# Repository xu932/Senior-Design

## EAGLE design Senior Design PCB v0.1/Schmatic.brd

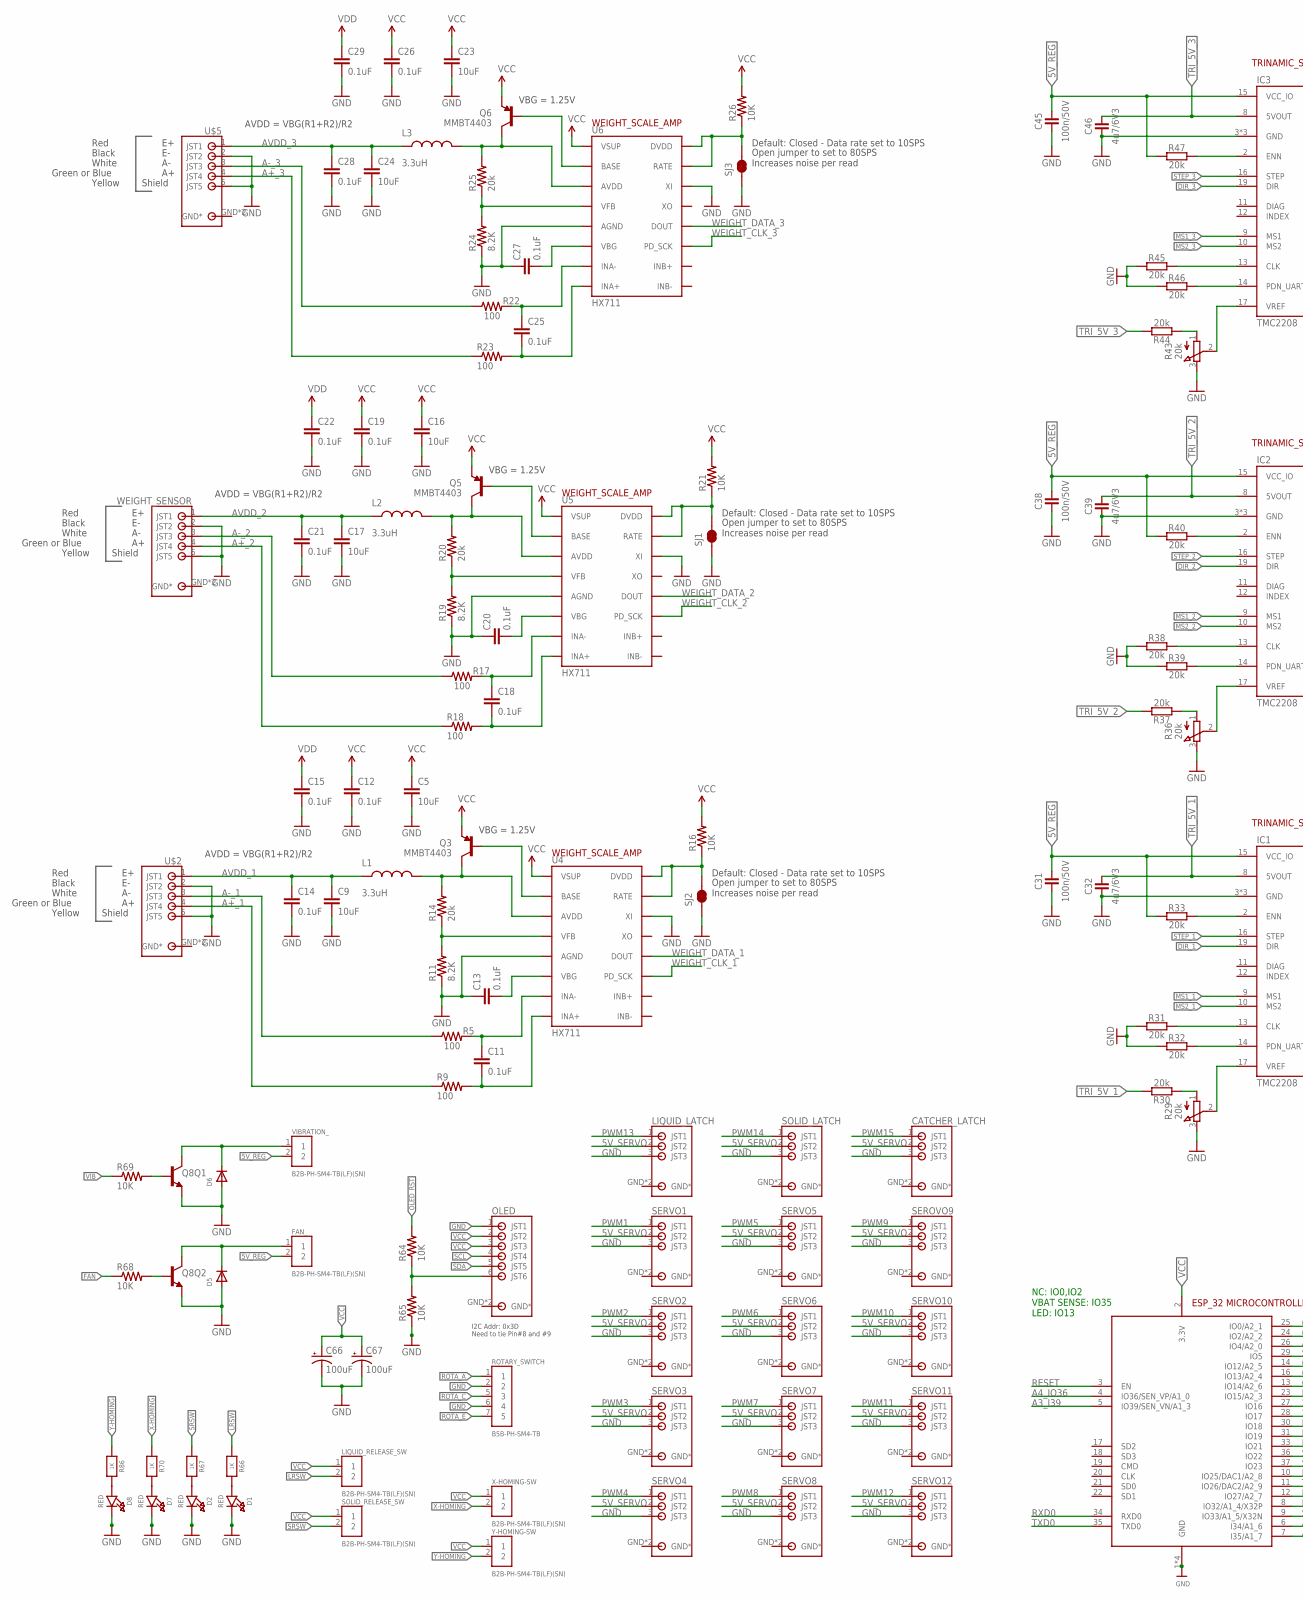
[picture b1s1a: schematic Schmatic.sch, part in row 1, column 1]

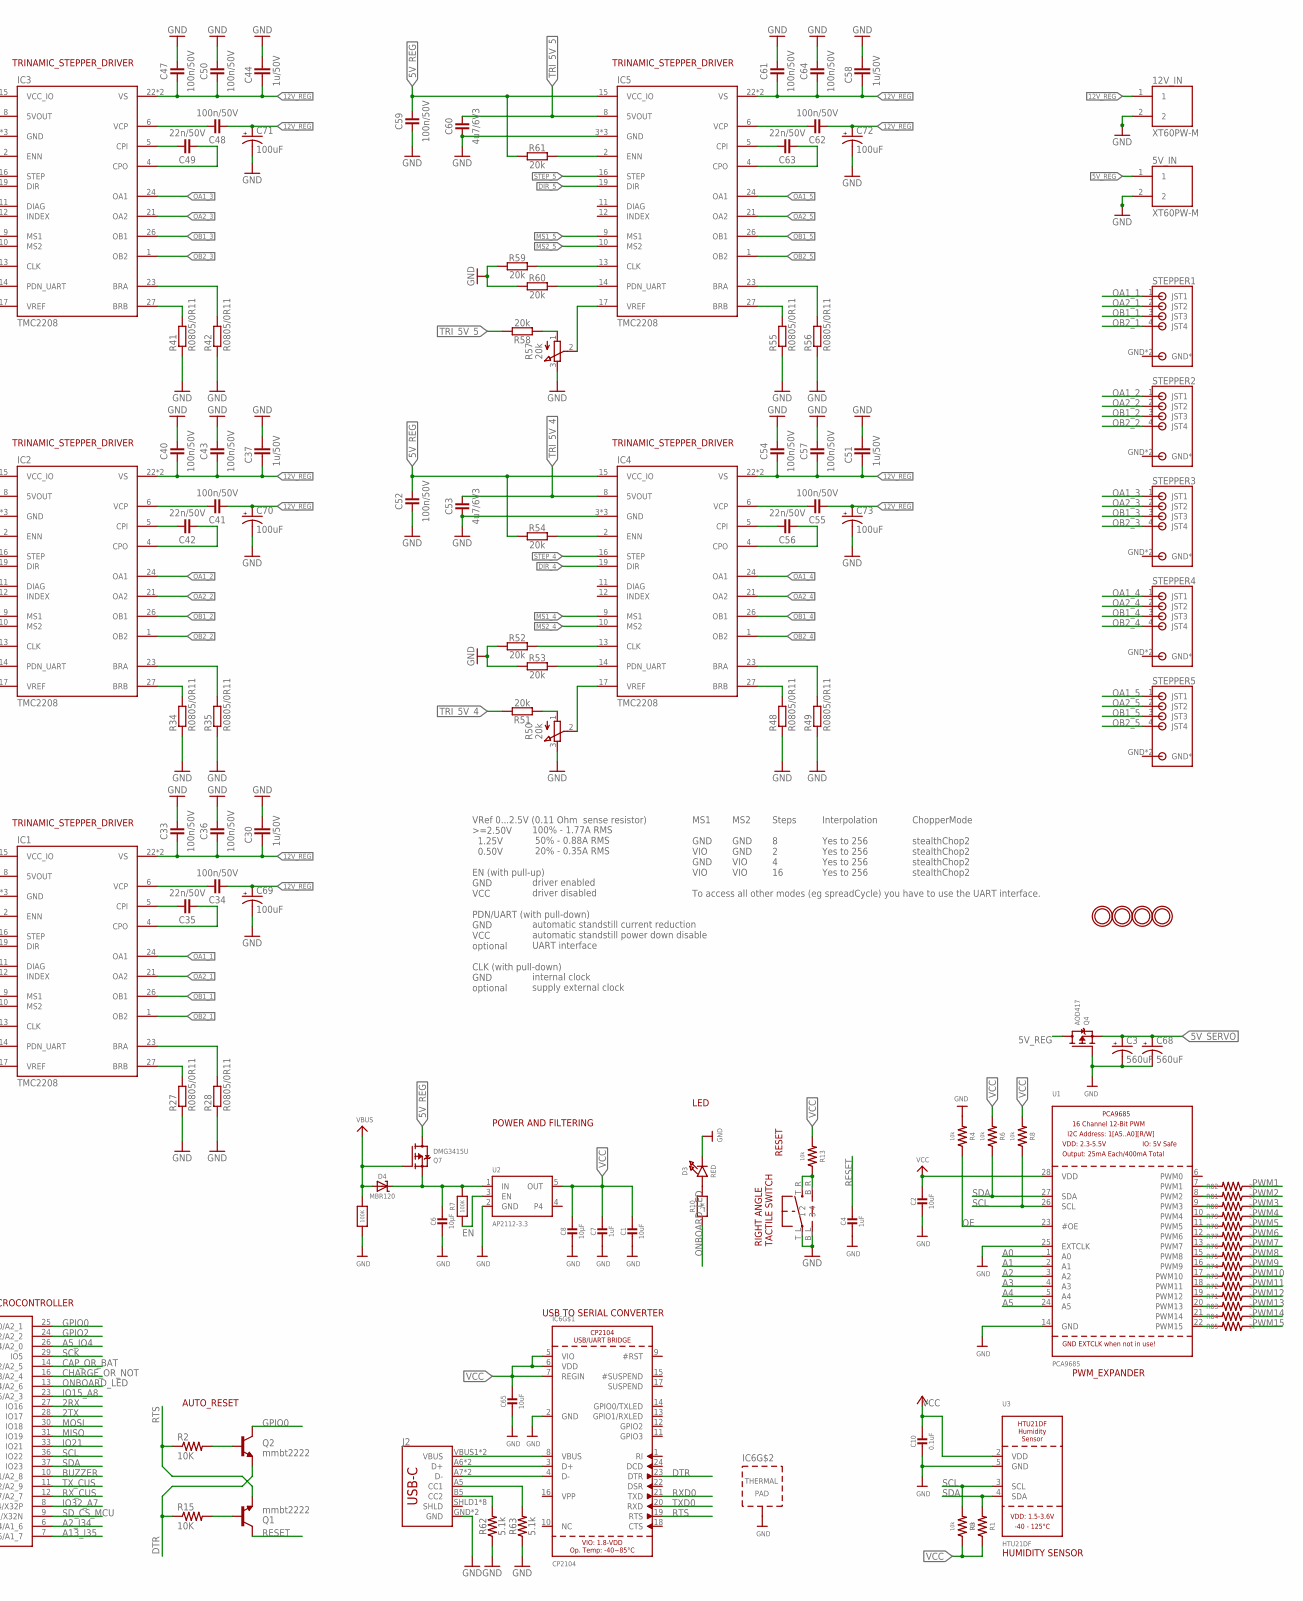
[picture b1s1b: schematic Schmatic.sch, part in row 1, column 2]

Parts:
5V_IN, 12V_IN: XT60PW-M; AMASS_XT60PW-M
C1, C2, C65: 10uF; 0805-NO
C3, C68: 560uF; PANASONIC_G
C4, C7: 1uF; 0603-NO
C5, C9, C16, C17, C23, C24: 10uF; 1210
C6, C8: 10µF; 0805-NO
C10: 0.1uF; 0805-NO
C11, C12, C13, C14, C15, C18, C19, C20, C21, C22, C25, C26, C27, C28, C29: 0.1uF; 0603-CAP
C30, C37, C44, C51, C58: 1u/50V; C0805
C31, C33, C34, C36, C38, C40, C41, C43, C45, C47, C48, C50, C52, C54, C55, C57, C59, C61, C62, C64: 100n/50V; C0402
C32, C39, C46, C53, C60: 4u7/6V3; C0402
C35, C42, C49, C56, C63: 22n/50V; C0402
C66, C67, C69, C70, C71, C72, C73: 100uF; PANASONIC_D
CATCHER_LATCH: S3B-PH-SM4_TB
D1, D2, D3, D7, D8: RED; CHIPLED_0805_NOOUTLINE
D4: MBR120; SOD-123
D5, D6: DIODESOD-323F; SOD-323F
FAN_: B2B-PH-SM4-TB(LF)(SN); JST_B2B-PH-SM4-TB(LF)(SN)
IC1, IC2, IC3, IC4, IC5: TMC2208; QFN28-PAD
IC6: CP2104; QFN24_4MM_SMSC
J2: USB_C16PIN; USB-C-16P
L1, L2, L3: 3.3uH; 0805
LIQUID_LATCH: S3B-PH-SM4_TB
LIQUID_RELEASE_SW: B2B-PH-SM4-TB(LF)(SN); JST_B2B-PH-SM4-TB(LF)(SN)
OLED: S6B-PH-SM4_TB
Q1, Q2: mmbt2222; SOT23-3
Q3, Q5, Q6: MMBT4403; SOT23-3
Q4: AOD417; TO252
Q7: DMG3415U; SOT23-R
Q8: TRANS_NPN_DUAL-MBT3904DW1T1; SC70-6
R1, R3, R4, R6, R8, R13: 10k; 0603
R2, R15, R16, R21, R26, R64, R65, R68, R69: 10K; 0603-RES
R5, R9, R17, R18, R22, R23: 100; 0603-RES
R7, R12: 100K; 0603-NO@1
R10, R66, R67, R70, R86: 1K; 0603-NO@1
R11, R19, R24: 8.2K; 0603-RES
R14, R20, R25: 20k; 0603-RES
R27, R28, R34, R35, R41, R42, R48, R49, R55, R56: R0805/0R11; M0805
R29, R36, R43, R50, R57: 20k; POT_EVM3R
R30, R31, R32, R33, R37, R38, R39, R40, R44, R45, R46, R47, R51, R52, R53, R54, R58, R59, R60, R61: 20k; C0402
R62, R63: 5.1k; 0603
R71, R72, R73, R74, R75, R76, R77, R78, R79, R80, R81, R82, R83, R84, R85: 22; 0603
ROTARY_SWITCH: B5B-PH-SM4-TB; JST_B5B-PH-SM4-TB
SEROVO9: S3B-PH-SM4_TB
SERVO1, SERVO2, SERVO3, SERVO4, SERVO5, SERVO6, SERVO7, SERVO8, SERVO10, SERVO11, SERVO12: S3B-PH-SM4_TB
SJ1, SJ2, SJ3: JUMPER-PAD-2-NC_BY_TRACE; PAD-JUMPER-2-NC_BY_TRACE_YES_SILK
SOLID_LATCH: S3B-PH-SM4_TB
SOLID_RELEASE_SW: B2B-PH-SM4-TB(LF)(SN); JST_B2B-PH-SM4-TB(LF)(SN)
STEPPER1, STEPPER2, STEPPER3, STEPPER4, STEPPER5: S4B-PH-SM4_TB
U1: PCA9685; TSSOP28
U2: AP2112-3.3; SOT23-5
U3: HTU21DF
U4, U5, U6: HX711; SO16
U$2, U$5: S5B-PH-SM4_TB
U$4, U$48, U$49, U$50: MOUNTINGHOLE2.5; MOUNTINGHOLE_2.5_PLATED
U$9: RIGHT_ANGLE_TACTILE_SWITCH
VIBRATION_: B2B-PH-SM4-TB(LF)(SN); JST_B2B-PH-SM4-TB(LF)(SN)
WEIGHT_SENSOR: S5B-PH-SM4_TB
X2: ESP32_WROOM32_SKINNY; WROOM32_SKINNY
X-HOMING-SW: B2B-PH-SM4-TB(LF)(SN); JST_B2B-PH-SM4-TB(LF)(SN)
Y-HOMING-SW: B2B-PH-SM4-TB(LF)(SN); JST_B2B-PH-SM4-TB(LF)(SN)

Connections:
2RX: X2.27 (IO16)
2TX: X2.28 (IO17)
5V_REG: 5V_IN.1, C31.2, C38.2, C45.2, C52.2, C59.2, FAN_.2, IC1.15 (VCC_IO), IC2.15 (VCC_IO), IC3.15 (VCC_IO), IC4.15 (VCC_IO), IC5.15 (VCC_IO), Q4.3 (D), Q7.3 (D), R33.1, R40.1, R47.1, R54.1, R61.1, VIBRATION_.2
5V_SERVO: C3.+, C68.+, CATCHER_LATCH.2 (JST2), LIQUID_LATCH.2 (JST2), Q4.2 (S), SEROVO9.2 (JST2), SERVO1.2 (JST2), SERVO2.2 (JST2), SERVO3.2 (JST2), SERVO4.2 (JST2), SERVO5.2 (JST2), SERVO6.2 (JST2), SERVO7.2 (JST2), SERVO8.2 (JST2), SERVO10.2 (JST2), SERVO11.2 (JST2), SERVO12.2 (JST2), SOLID_LATCH.2 (JST2)
12V_REG: 12V_IN.1, C30.1, C33.1, C34.1, C36.1, C37.1, C40.1, C41.1, C43.1, C44.1, C47.1, C48.1, C50.1, C51.1, C54.1, C55.1, C57.1, C58.1, C61.1, C62.1, C64.1, C69.+, C70.+, C71.+, C72.+, C73.+, IC1.22 (VS), IC1.28 (VS), IC2.22 (VS), IC2.28 (VS), IC3.22 (VS), IC3.28 (VS), IC4.22 (VS), IC4.28 (VS), IC5.22 (VS), IC5.28 (VS)
A0: U1.1 (A0)
A1: U1.2 (A1)
A2: U1.3 (A2)
A2_I34: X2.6 (I34/A1_6)
A3: U1.4 (A3)
A3_I39: X2.5 (IO39/SEN_VN/A1_3)
A4: U1.5 (A4)
A4_IO36: X2.4 (IO36/SEN_VP/A1_0)
A5: U1.24 (A5)
A5_IO4: X2.26 (IO4/A2_0)
A13_I35: X2.7 (I35/A1_7)
A+_1: R9.1, U$2.4 (JST4)
A+_2: R18.1, WEIGHT_SENSOR.4 (JST4)
A+_3: R23.1, U$5.4 (JST4)
A-_1: R5.1, U$2.3 (JST3)
A-_2: R17.1, WEIGHT_SENSOR.3 (JST3)
A-_3: R22.1, U$5.3 (JST3)
AVDD_1: C9.1, C14.1, L1.1, U$2.1 (JST1)
AVDD_2: C17.1, C21.1, L2.1, WEIGHT_SENSOR.1 (JST1)
AVDD_3: C24.1, C28.1, L3.1, U$5.1 (JST1)
BRA: IC1.23 (BRA), R28.2
BRA1: IC2.23 (BRA), R35.2
BRA2: IC3.23 (BRA), R42.2
BRA3: IC4.23 (BRA), R49.2
BRA4: IC5.23 (BRA), R56.2
BRB: IC1.27 (BRB), R27.2
BRB1: IC2.27 (BRB), R34.2
BRB2: IC3.27 (BRB), R41.2
BRB3: IC4.27 (BRB), R48.2
BRB4: IC5.27 (BRB), R55.2
BUZZER: X2.10 (IO25/DAC1/A2_8)
CAP_OR_BAT: X2.14 (IO12/A2_5)
CC1: J2.A5 (CC1), R63.2
CC2: J2.B5 (CC2), R62.2
CHARGE_OR_NOT: X2.16 (IO13/A2_4)
CLK_1: IC1.13 (CLK), R31.2
CLK_2: IC2.13 (CLK), R38.2
CLK_3: IC3.13 (CLK), R45.2
CLK_4: IC4.13 (CLK), R52.2
CLK_5: IC5.13 (CLK), R59.2
CPI: C35.2, IC1.5 (CPI)
CPI1: C42.2, IC2.5 (CPI)
CPI2: C49.2, IC3.5 (CPI)
CPI3: C56.2, IC4.5 (CPI)
CPI4: C63.2, IC5.5 (CPI)
CPO: C35.1, IC1.4 (CPO)
CPO1: C42.1, IC2.4 (CPO)
CPO2: C49.1, IC3.4 (CPO)
CPO3: C56.1, IC4.4 (CPO)
CPO4: C63.1, IC5.4 (CPO)
DIR_1: IC1.19 (DIR)
DIR_2: IC2.19 (DIR)
DIR_3: IC3.19 (DIR)
DIR_4: IC4.19 (DIR)
DIR_5: IC5.19 (DIR)
DTR: IC6.23 (DTR), Q2.2 (E), R15.1
EN: R7.1, U2.3 (EN)
EN_1: IC1.2 (ENN), R33.2
EN_2: IC2.2 (ENN), R40.2
EN_3: IC3.2 (ENN), R47.2
EN_4: IC4.2 (ENN), R54.2
EN_5: IC5.2 (ENN), R61.2
FAN: R68.1
FAN_5V: D5.C, FAN_.1, Q8.6 (C)
GND: 5V_IN.2, 12V_IN.2, C1.2, C2.2, C3.-, C4.2, C5.2, C6.2, C7.2, C8.2, C9.2, C10.2, C12.2, C13.1, C14.2, C15.2, C16.2, C17.2, C19.2, C20.1, C21.2, C22.2, C23.2, C24.2, C26.2, C27.1, C28.2, C29.2, C30.2, C31.1, C32.1, C33.2, C36.2, C37.2, C38.1, C39.1, C40.2, C43.2, C44.2, C45.1, C46.1, C47.2, C50.2, C51.2, C52.1, C53.1, C54.2, C57.2, C58.2, C59.1, C60.1, C61.2, C64.2, C65.2, C66.-, C67.-, C68.-, C69.-, C70.-, C71.-, C72.-, C73.-, CATCHER_LATCH.3 (JST3), D1.C, D2.C, D3.C, D5.A, D6.A, D7.C, D8.C, IC1.3 (GND), IC1.18 (GND), IC1.TP (GND), IC2.3 (GND), IC2.18 (GND), IC2.TP (GND), IC3.3 (GND), IC3.18 (GND), IC3.TP (GND), IC4.3 (GND), IC4.18 (GND), IC4.TP (GND), IC5.3 (GND), IC5.18 (GND), IC5.TP (GND), IC6.2 (GND), IC6.THERM (TP), J2.GND, J2.GND2 (GND), LIQUID_LATCH.3 (JST3), OLED.1 (JST1), Q4.1 (G), Q8.1 (E), Q8.4 (E), R4.2, R11.1, R12.1, R19.1, R24.1, R27.1, R28.1, R29.3 (E), R31.1, R32.1, R34.1, R35.1, R36.3 (E), R38.1, R39.1, R41.1, R42.1, R43.3 (E), R45.1, R46.1, R48.1, R49.1, R50.3 (E), R52.1, R53.1, R55.1, R56.1, R57.3 (E), R59.1, R60.1, R62.1, R63.1, R65.1, ROTARY_SWITCH.2, ROTARY_SWITCH.6 (4), SEROVO9.3 (JST3), SERVO1.3 (JST3), SERVO2.3 (JST3), SERVO3.3 (JST3), SERVO4.3 (JST3), SERVO5.3 (JST3), SERVO6.3 (JST3), SERVO7.3 (JST3), SERVO8.3 (JST3), SERVO10.3 (JST3), SERVO11.3 (JST3), SERVO12.3 (JST3), SJ1.1, SJ2.1, SJ3.1, SOLID_LATCH.3 (JST3), U1.14 (GND), U1.25 (EXTCLK), U2.2 (GND), U3.5 (GND), U4.5 (AGND), U4.14 (XI), U5.5 (AGND), U5.14 (XI), U6.5 (AGND), U6.14 (XI), U$2.2 (JST2), U$2.5 (JST5), U$5.2 (JST2), U$5.5 (JST5), U$9.B_L (3), U$9.T_L (1), WEIGHT_SENSOR.2 (JST2), WEIGHT_SENSOR.5 (JST5), X2.1 (GND), X2.15 (GND), X2.38 (GND), X2.P$1 (GND)
GPIO0: Q2.3 (C), X2.25 (IO0/A2_1)
GPIO2: X2.24 (IO2/A2_2)
IO15_A8: X2.23 (IO15/A2_3)
IO21: X2.33 (IO21)
IO32_A7: X2.8 (IO32/A1_4/X32P)
LRSW: LIQUID_RELEASE_SW.2, R66.1
MISO: X2.31 (IO19)
MOSI: X2.30 (IO18)
MS1_1: IC1.9 (MS1)
MS1_2: IC2.9 (MS1)
MS1_3: IC3.9 (MS1)
MS1_4: IC4.9 (MS1)
MS1_5: IC5.9 (MS1)
MS2_1: IC1.10 (MS2)
MS2_2: IC2.10 (MS2)
MS2_3: IC3.10 (MS2)
MS2_4: IC4.10 (MS2)
MS2_5: IC5.10 (MS2)
unnamed: C13.2, U4.6 (VBG)
unnamed: L1.2, Q3.3 (C), R14.2, U4.3 (AVDD)
unnamed: Q5.1 (B), U5.2 (BASE)
unnamed: Q3.1 (B), U4.2 (BASE)
unnamed: D3.A, R10.2
unnamed: R11.2, R14.1, U4.4 (VFB)
unnamed: C6.1, D4.C, Q7.2 (S), R7.2, U2.1 (IN)
unnamed: C11.1, R5.2, U4.7 (INA-)
unnamed: C11.2, R9.2, U4.8 (INA+)
unnamed: R16.1, SJ2.2, U4.15 (RATE), U4.16 (DVDD)
unnamed: R19.2, R20.1, U5.4 (VFB)
unnamed: Q1.1 (B), R15.2
unnamed: Q2.1 (B), R2.2
unnamed: C20.2, U5.6 (VBG)
unnamed: L2.2, Q5.3 (C), R20.2, U5.3 (AVDD)
unnamed: C18.1, R17.2, U5.7 (INA-)
unnamed: C18.2, R18.2, U5.8 (INA+)
unnamed: R21.1, SJ1.2, U5.15 (RATE), U5.16 (DVDD)
unnamed: Q6.1 (B), U6.2 (BASE)
unnamed: R24.2, R25.1, U6.4 (VFB)
unnamed: C27.2, U6.6 (VBG)
unnamed: L3.2, Q6.3 (C), R25.2, U6.3 (AVDD)
unnamed: C25.1, R22.2, U6.7 (INA-)
unnamed: C25.2, R23.2, U6.8 (INA+)
unnamed: R26.1, SJ3.2, U6.15 (RATE), U6.16 (DVDD)
unnamed: IC6.8 (VBUS), J2.VBUS1 (VBUS), J2.VBUS2 (VBUS)
unnamed: IC6.3 (D+), J2.A6 (D+), J2.B6 (D+)
unnamed: IC6.4 (D-), J2.A7 (D-), J2.B7 (D-)
unnamed: D1.A, R66.2
unnamed: OLED.6 (JST6), R64.1, R65.2
unnamed: Q8.5 (B), R69.2
unnamed: D2.A, R67.2
unnamed: Q8.2 (B), R68.2
unnamed: R71.2, U1.19 (PWM12)
unnamed: R72.2, U1.18 (PWM11)
unnamed: R73.2, U1.17 (PWM10)
unnamed: R74.2, U1.16 (PWM9)
unnamed: R75.2, U1.15 (PWM8)
unnamed: R76.2, U1.13 (PWM7)
unnamed: R77.2, U1.12 (PWM6)
unnamed: R78.2, U1.11 (PWM5)
unnamed: R79.2, U1.10 (PWM4)
unnamed: R80.2, U1.9 (PWM3)
unnamed: R81.2, U1.8 (PWM2)
unnamed: R82.2, U1.7 (PWM1)
unnamed: R83.2, U1.20 (PWM13)
unnamed: R84.2, U1.21 (PWM14)
unnamed: R85.2, U1.22 (PWM15)
unnamed: D7.A, R70.2
unnamed: R13.1, U$9.B_R (4), U$9.T_R (2)
unnamed: D8.A, R86.2
OA1_1: IC1.24 (OA1), STEPPER1.1 (JST1)
OA1_2: IC2.24 (OA1), STEPPER2.1 (JST1)
OA1_3: IC3.24 (OA1), STEPPER3.1 (JST1)
OA1_4: IC4.24 (OA1), STEPPER4.1 (JST1)
OA1_5: IC5.24 (OA1), STEPPER5.1 (JST1)
OA2_1: IC1.21 (OA2), STEPPER1.2 (JST2)
OA2_2: IC2.21 (OA2), STEPPER2.2 (JST2)
OA2_3: IC3.21 (OA2), STEPPER3.2 (JST2)
OA2_4: IC4.21 (OA2), STEPPER4.2 (JST2)
OA2_5: IC5.21 (OA2), STEPPER5.2 (JST2)
OB1_1: IC1.26 (OB1), STEPPER1.3 (JST3)
OB1_2: IC2.26 (OB1), STEPPER2.3 (JST3)
OB1_3: IC3.26 (OB1), STEPPER3.3 (JST3)
OB1_4: IC4.26 (OB1), STEPPER4.3 (JST3)
OB1_5: IC5.26 (OB1), STEPPER5.3 (JST3)
OB2_1: IC1.1 (OB2), STEPPER1.4 (JST4)
OB2_2: IC2.1 (OB2), STEPPER2.4 (JST4)
OB2_3: IC3.1 (OB2), STEPPER3.4 (JST4)
OB2_4: IC4.1 (OB2), STEPPER4.4 (JST4)
OB2_5: IC5.1 (OB2), STEPPER5.4 (JST4)
OE: R4.1, U1.23 (#OE)
OLED_RST: R64.2
ONBOARD_LED: R10.1, X2.13 (IO14/A2_6)
PDN_UART_1: IC1.14 (PDN_UART), R32.2
PDN_UART_2: IC2.14 (PDN_UART), R39.2
PDN_UART_3: IC3.14 (PDN_UART), R46.2
PDN_UART_4: IC4.14 (PDN_UART), R53.2
PDN_UART_5: IC5.14 (PDN_UART), R60.2
PWM1: R82.1, SERVO1.1 (JST1)
PWM2: R81.1, SERVO2.1 (JST1)
PWM3: R80.1, SERVO3.1 (JST1)
PWM4: R79.1, SERVO4.1 (JST1)
PWM5: R78.1, SERVO5.1 (JST1)
PWM6: R77.1, SERVO6.1 (JST1)
PWM7: R76.1, SERVO7.1 (JST1)
PWM8: R75.1, SERVO8.1 (JST1)
PWM9: R74.1, SEROVO9.1 (JST1)
PWM10: R73.1, SERVO10.1 (JST1)
PWM11: R72.1, SERVO11.1 (JST1)
PWM12: R71.1, SERVO12.1 (JST1)
PWM13: LIQUID_LATCH.1 (JST1), R83.1
PWM14: R84.1, SOLID_LATCH.1 (JST1)
PWM15: CATCHER_LATCH.1 (JST1), R85.1
RESET: C4.1, Q1.3 (C), X2.3 (EN)
ROTA_A: ROTARY_SWITCH.1
ROTA_C: ROTARY_SWITCH.5 (3)
ROTA_E: ROTARY_SWITCH.7 (5)
RTS: IC6.19 (RTS), Q1.2 (E), R2.1
RXD0: IC6.21 (TXD), X2.34 (RXD0)
RX_CUS: X2.12 (IO27/A2_7)
SCK: X2.29 (IO5)
SCL: OLED.4 (JST4), R3.2, R8.1, U1.26 (SCL), U3.3 (SCL), X2.36 (IO22)
SDA: OLED.5 (JST5), R1.2, R6.1, U1.27 (SDA), U3.4 (SDA), X2.37 (IO23)
SD_CS_MCU: X2.9 (IO33/A1_5/X32N)
SRSW: R67.1, SOLID_RELEASE_SW.2
STEP_1: IC1.16 (STEP)
STEP_2: IC2.16 (STEP)
STEP_3: IC3.16 (STEP)
STEP_4: IC4.16 (STEP)
STEP_5: IC5.16 (STEP)
TRI_5V_1: C32.2, IC1.8 (5VOUT), R30.2
TRI_5V_2: C39.2, IC2.8 (5VOUT), R37.2
TRI_5V_3: C46.2, IC3.8 (5VOUT), R44.2
TRI_5V_4: C53.2, IC4.8 (5VOUT), R51.2
TRI_5V_5: C60.2, IC5.8 (5VOUT), R58.2
TXD0: IC6.20 (RXD), X2.35 (TXD0)
TX_CUS: X2.11 (IO26/DAC2/A2_9)
VBUS: D4.A, Q7.1 (G), R12.2
VCC: C1.1, C2.1, C5.1, C7.1, C8.1, C10.1, C12.1, C16.1, C19.1, C23.1, C26.1, C65.1, C66.+, C67.+, IC6.5 (VIO), IC6.6 (VDD), IC6.7 (REGIN), LIQUID_RELEASE_SW.1, OLED.2 (JST2), OLED.3 (JST3), Q3.2 (E), Q5.2 (E), Q6.2 (E), R1.1, R3.1, R6.2, R8.2, R13.2, R16.2, R21.2, R26.2, SOLID_RELEASE_SW.1, U1.28 (VDD), U2.5 (OUT), U3.2 (VDD), U4.1 (VSUP), U5.1 (VSUP), U6.1 (VSUP), X2.2 (3.3V), X-HOMING-SW.1, Y-HOMING-SW.1
VCP: C34.2, IC1.6 (VCP)
VCP1: C41.2, IC2.6 (VCP)
VCP2: C48.2, IC3.6 (VCP)
VCP3: C55.2, IC4.6 (VCP)
VCP4: C62.2, IC5.6 (VCP)
VDD: C15.1, C22.1, C29.1
VIB: R69.1
VIB_5V: D6.C, Q8.3 (C), VIBRATION_.1
VREF: IC1.17 (VREF), R29.2 (S)
VREF1: R29.1 (A), R30.1
VREF2: IC2.17 (VREF), R36.2 (S)
VREF3: R36.1 (A), R37.1
VREF4: IC3.17 (VREF), R43.2 (S)
VREF5: R43.1 (A), R44.1
VREF6: IC4.17 (VREF), R50.2 (S)
VREF7: R50.1 (A), R51.1
VREF8: IC5.17 (VREF), R57.2 (S)
VREF9: R57.1 (A), R58.1
WEIGHT_CLK_1: U4.11 (PD_SCK)
WEIGHT_CLK_2: U5.11 (PD_SCK)
WEIGHT_CLK_3: U6.11 (PD_SCK)
WEIGHT_DATA_1: U4.12 (DOUT)
WEIGHT_DATA_2: U5.12 (DOUT)
WEIGHT_DATA_3: U6.12 (DOUT)
X-HOMING: R70.1, X-HOMING-SW.2
Y-HOMING: R86.1, Y-HOMING-SW.2

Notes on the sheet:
NC: IO0,IO2 VBAT SENSE: IO35 LED: IO13
POWER AND FILTERING
RESET
LED
VBG = 1.25V
AVDD = VBG(R1+R2)/R2
Default: Closed - Data rate set to 10SPS
Open jumper to set to 80SPS Increases noise per read
Red
Black
White
Green or Blue
Shield
Yellow
VRef 0...2.5V (0.11 Ohm sense resistor) >=2.50V 1.25V 0.50V EN (with pull-up) GND VCC PDN/UART (with pull-down) GND VCC optional CLK (with pull-down) GND optional
100% - 1.77A RMS 50% - 0.88A RMS 20% - 0.35A RMS driver enabled driver disabled automatic standstill current reduction automatic standstill power down disable UART interface internal clock supply external clock
MS1 GND VIO GND VIO To access all other modes (eg spreadCycle) you have to use the UART interface.
MS2 GND GND VIO VIO
Steps 8 2 4 16
Interpolation Yes to 256 Yes to 256 Yes to 256 Yes to 256
ChopperMode stealthChop2 stealthChop2 stealthChop2 stealthChop2
USB TO SERIAL CONVERTER
I2C Addr: 0x3D Need to tie Pin#8 and #9
PWM_EXPANDER
HUMIDITY SENSOR
TRINAMIC_STEPPER_DRIVER
WEIGHT_SCALE_AMP
ESP_32 MICROCONTROLLER
AUTO_RESET

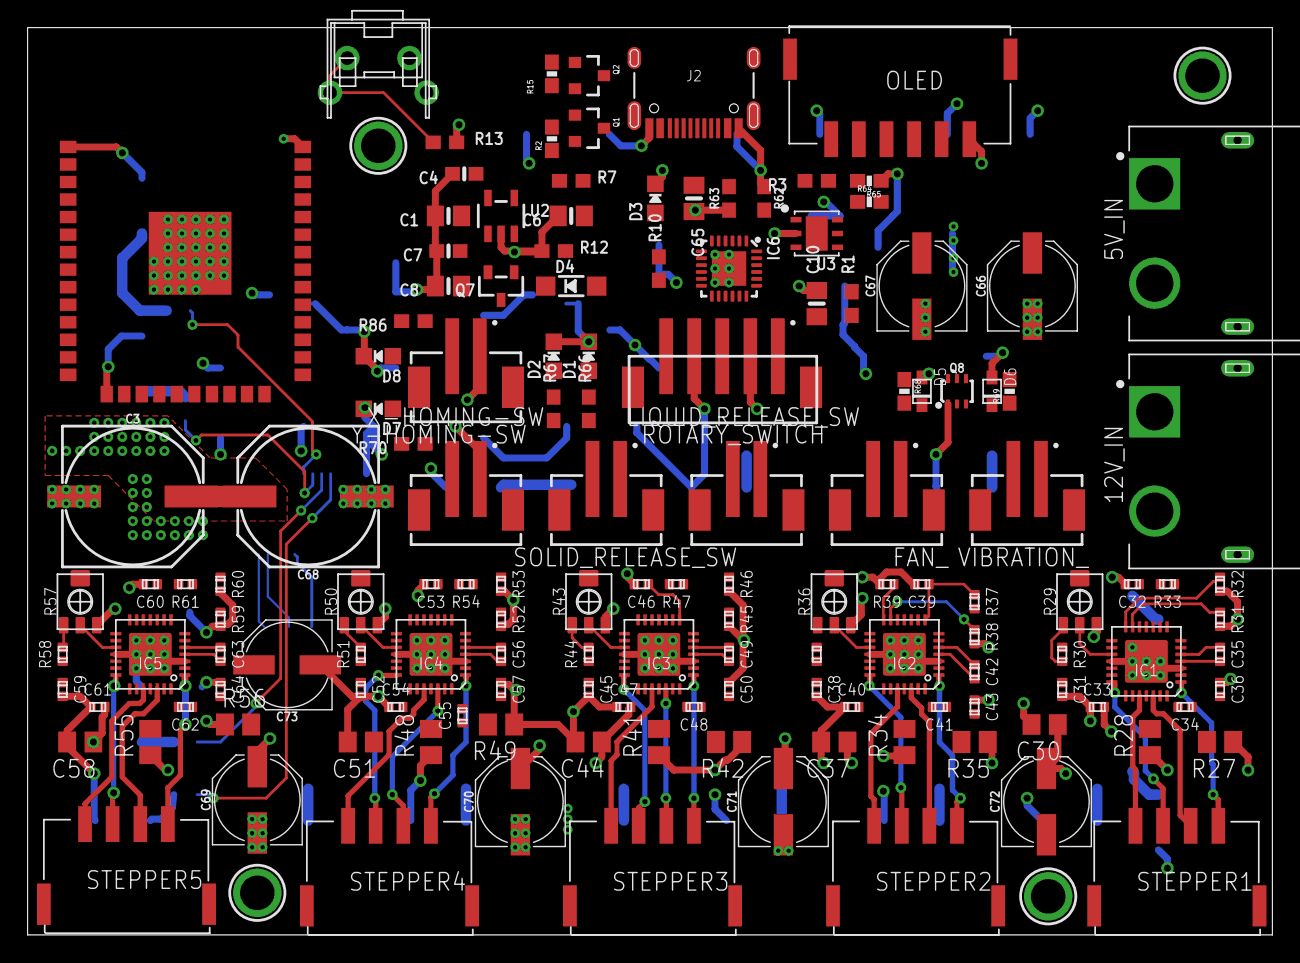
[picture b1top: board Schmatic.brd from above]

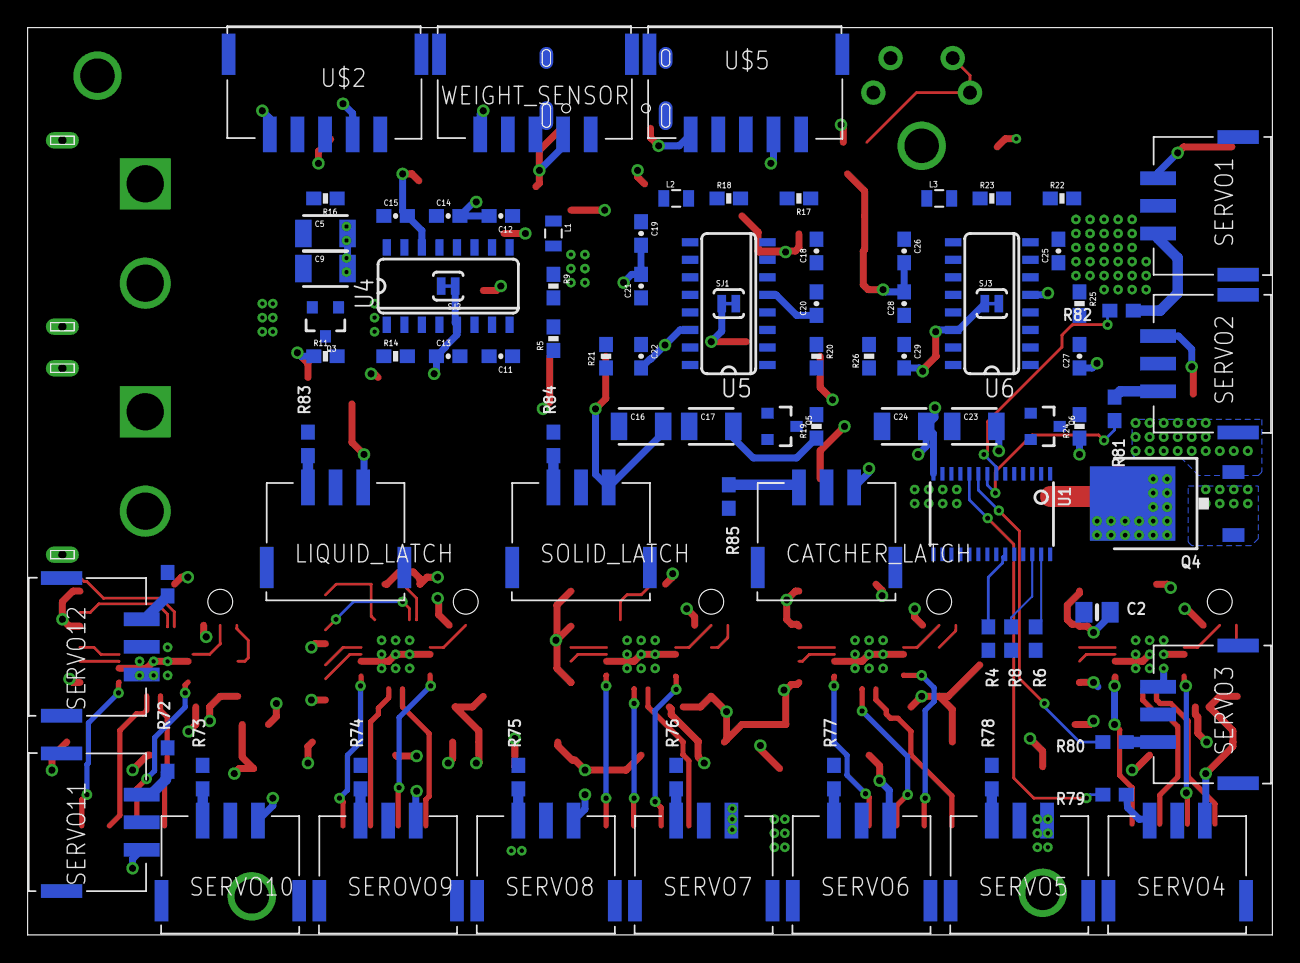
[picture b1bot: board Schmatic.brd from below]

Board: 4 copper layers, 90.1 x 65.7 mm, 233 parts (87 on the bottom side), 176 nets.

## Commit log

2019-09-18 done layout, waiting for signal wire pin config
2019-09-19 update pcb layout, finishedd net class assignment. assigned gnd plane, signal plane and Vref plane
2019-09-27 phase 1 code - add pwm and adc
2019-09-29 oops, forgot to add the files
2019-09-29 added hx711 reading functionality
2019-11-03 added htu21d-f humidity sensor and modified previous functions
2019-11-03 added oled display code
2019-12-14 updated repo with source code used for demo
2019-12-14 added ios app for bluetooth communication

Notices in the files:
parts and their libraries:
microbuilder: This work is placed in the public domain, and may be freely used for commercial and non-commercial work with the following conditions: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
SparkFun: Licensing: CC v3.0 Share-Alike You are welcome to use this library for commercial purposes.
